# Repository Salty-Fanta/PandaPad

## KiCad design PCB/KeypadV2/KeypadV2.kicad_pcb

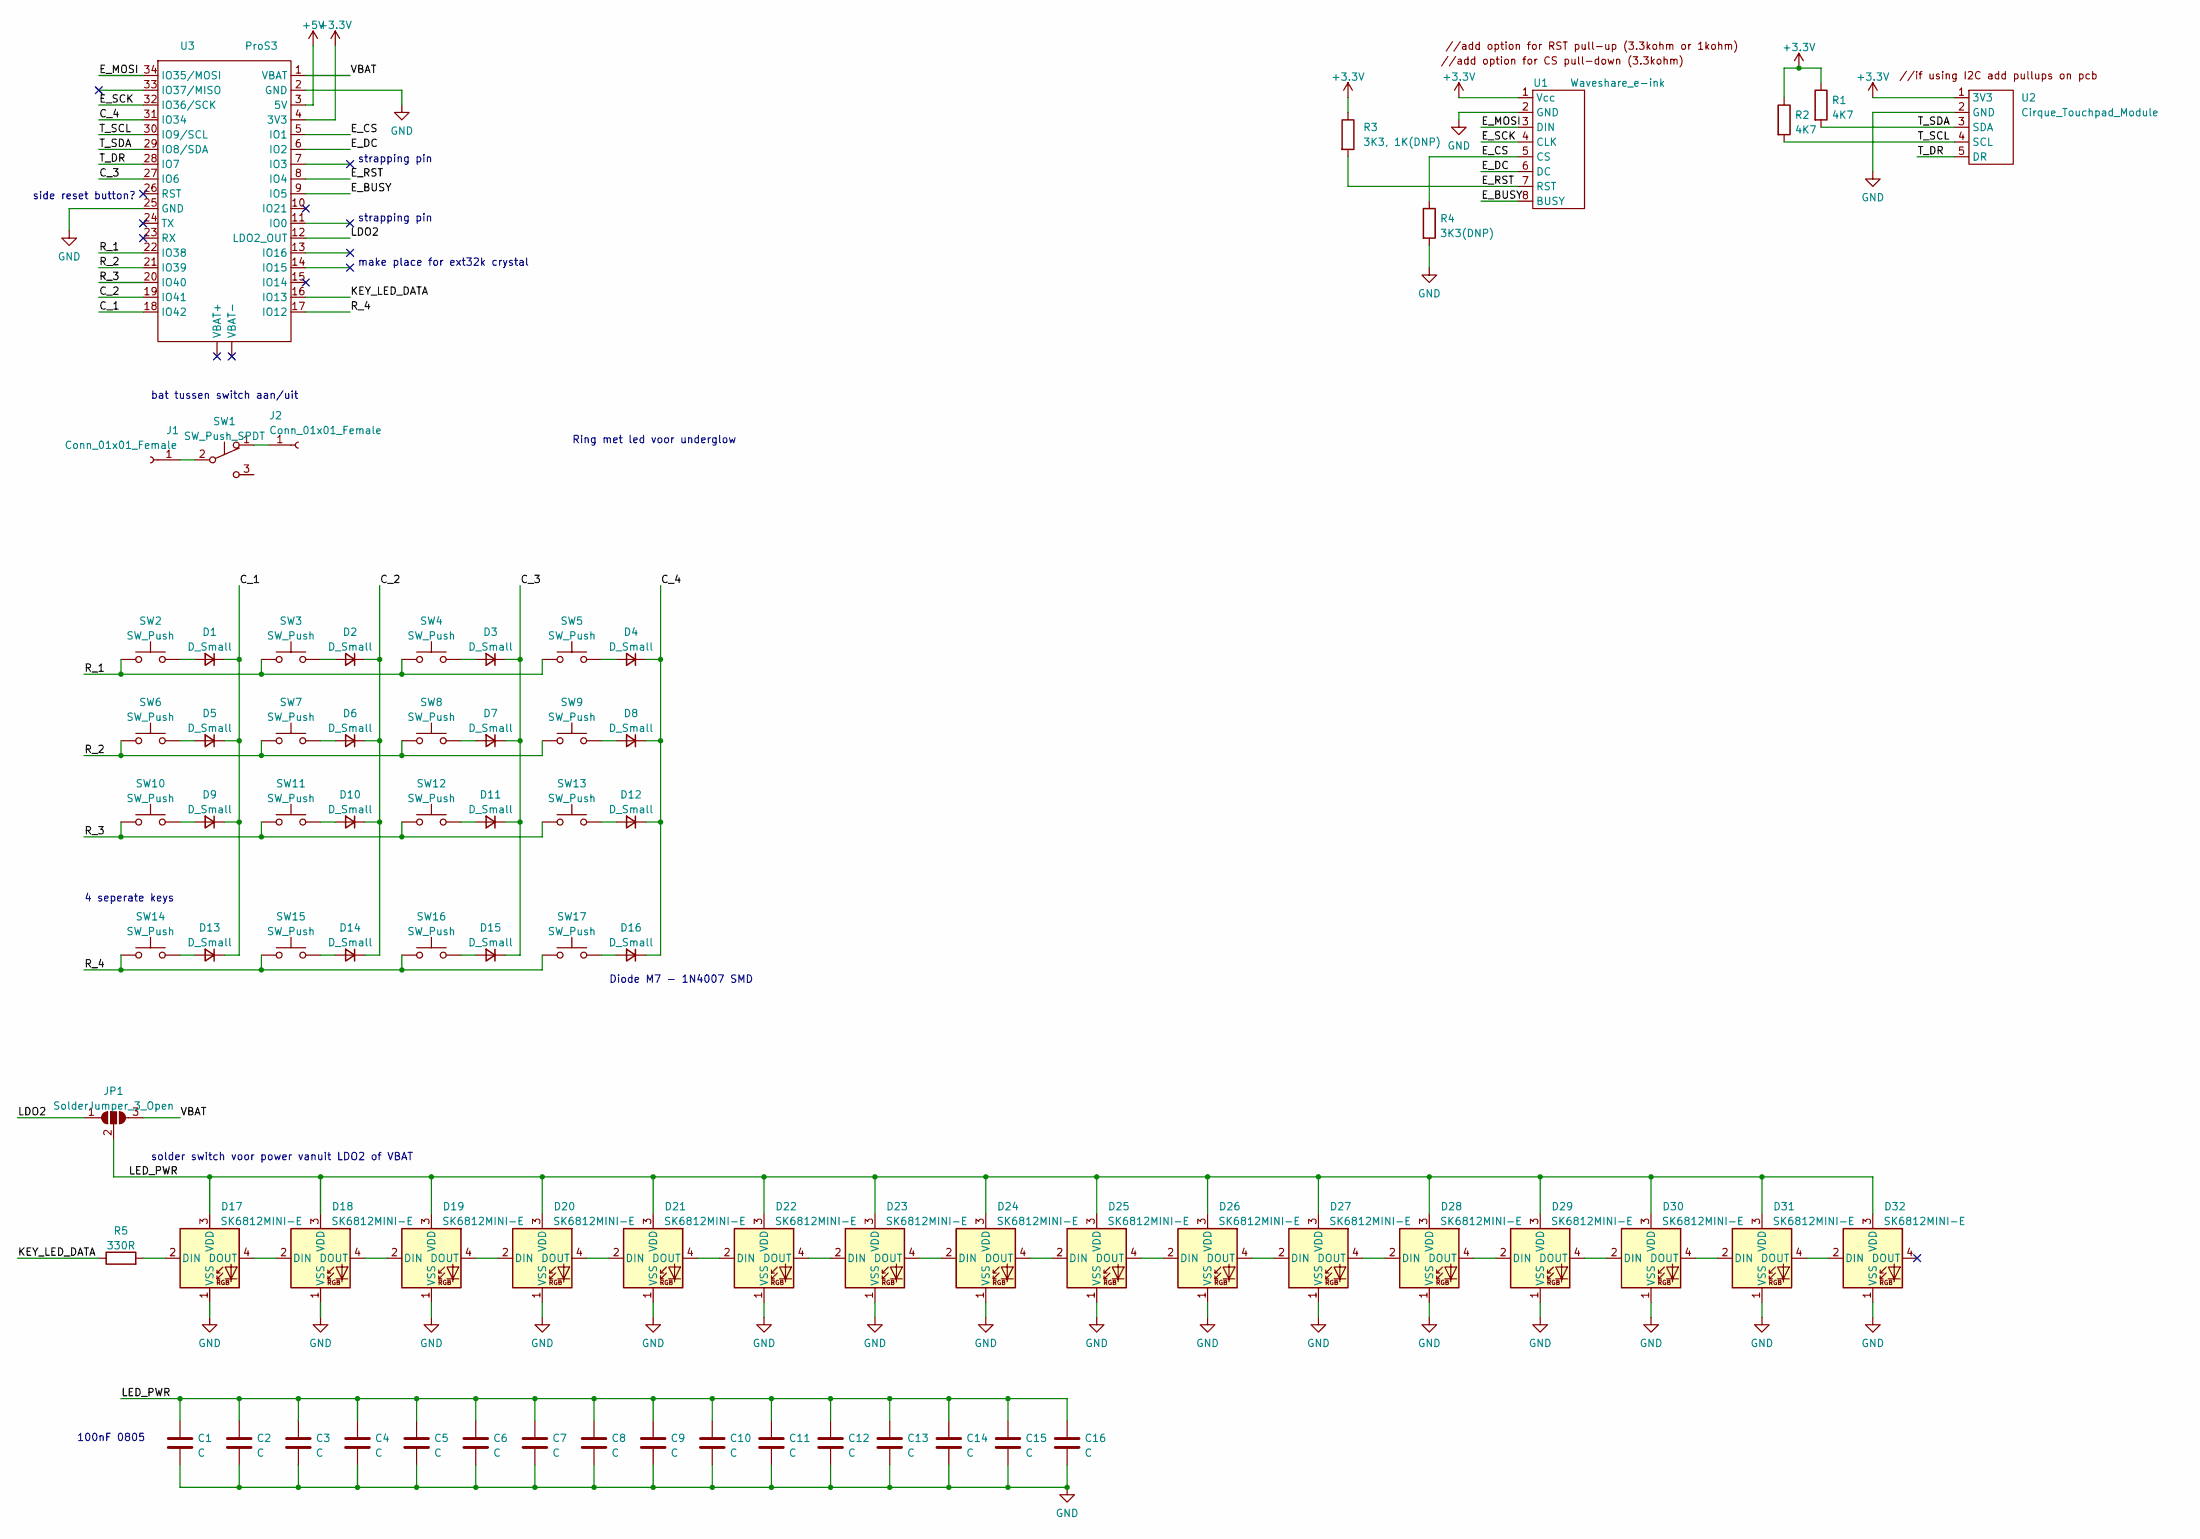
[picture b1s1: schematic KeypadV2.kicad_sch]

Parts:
C1, C2, C3, C4, C5, C6, C7, C8, C9, C10, C11, C12, C13, C14, C15, C16: C; C_0805_2012Metric_Pad1.18x1.45mm_HandSolder
D1, D2, D3, D4, D5, D6, D7, D8, D9, D10, D11, D12, D13, D14, D15, D16: D_Small; D_SOD-123
D17, D18, D19, D20, D21, D22, D23, D24, D25, D26, D27, D28, D29, D30, D31, D32: SK6812MINI-E; SK6812mini
J1, J2: Conn_01x01_Female; PinHeader_1x01_P2.54mm_Vertical
JP1: SolderJumper_3_Open; SolderJumper-3_P1.3mm_Open_Pad1.0x1.5mm
R1, R2: 4K7; R_0805_2012Metric_Pad1.20x1.40mm_HandSolder
R3: 3K3, 1K(DNP); R_0805_2012Metric_Pad1.20x1.40mm_HandSolder
R4: 3K3(DNP); R_0805_2012Metric_Pad1.20x1.40mm_HandSolder
R5: 330R; R_0805_2012Metric_Pad1.20x1.40mm_HandSolder
SW1: SW_Push_SPDT; PinHeader_1x03_P2.54mm_Vertical
SW2, SW3, SW4, SW5, SW6, SW7, SW8, SW9, SW10, SW11, SW12, SW13, SW14, SW15, SW16, SW17: SW_Push; Kailh_socket_MX
U1: Waveshare_e-ink; PinHeader_1x08_P2.54mm_Vertical
U2: Cirque_Touchpad_Module; PinHeader_1x05_P2.54mm_Vertical
U3: ProS3; ProS3_SMD

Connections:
+3.3V: R1.1, R2.1, R3.1, U1.1 (Vcc), U2.1 (3V3), U3.4 (3V3)
+5V: U3.3 (5V)
/C_1: D1.1 (K), D5.1 (K), D9.1 (K), D13.1 (K), U3.18 (IO42)
/C_2: D2.1 (K), D6.1 (K), D10.1 (K), D14.1 (K), U3.19 (IO41)
/C_3: D3.1 (K), D7.1 (K), D11.1 (K), D15.1 (K), U3.27 (IO6)
/C_4: D4.1 (K), D8.1 (K), D12.1 (K), D16.1 (K), U3.31 (IO34)
/E_BUSY: U1.8 (BUSY), U3.9 (IO5)
/E_CS: R4.1, U1.5 (CS), U3.5 (IO1)
/E_DC: U1.6 (DC), U3.6 (IO2)
/E_MOSI: U1.3 (DIN), U3.34 (IO35/MOSI)
/E_RST: R3.2, U1.7 (RST), U3.8 (IO4)
/E_SCK: U1.4 (CLK), U3.32 (IO36/SCK)
/KEY_LED_DATA: R5.1, U3.16 (IO13)
/LDO2: JP1.1 (A), U3.12 (LDO2_OUT)
/LED_PWR: C1.1, C2.1, C3.1, C4.1, C5.1, C6.1, C7.1, C8.1, C9.1, C10.1, C11.1, C12.1, C13.1, C14.1, C15.1, C16.1, D17.3 (VDD), D18.3 (VDD), D19.3 (VDD), D20.3 (VDD), D21.3 (VDD), D22.3 (VDD), D23.3 (VDD), D24.3 (VDD), D25.3 (VDD), D26.3 (VDD), D27.3 (VDD), D28.3 (VDD), D29.3 (VDD), D30.3 (VDD), D31.3 (VDD), D32.3 (VDD), JP1.2 (C)
/R_1: SW2.1, SW3.1, SW4.1, SW5.1, U3.22 (IO38)
/R_2: SW6.1, SW7.1, SW8.1, SW9.1, U3.21 (IO39)
/R_3: SW10.1, SW11.1, SW12.1, SW13.1, U3.20 (IO40)
/R_4: SW14.1, SW15.1, SW16.1, SW17.1, U3.17 (IO12)
/T_DR: U2.5 (DR), U3.28 (IO7)
/T_SCL: R2.2, U2.4 (SCL), U3.30 (IO9/SCL)
/T_SDA: R1.2, U2.3 (SDA), U3.29 (IO8/SDA)
/VBAT: JP1.3 (B), U3.1 (VBAT)
GND: C1.2, C2.2, C3.2, C4.2, C5.2, C6.2, C7.2, C8.2, C9.2, C10.2, C11.2, C12.2, C13.2, C14.2, C15.2, C16.2, D17.1 (VSS), D18.1 (VSS), D19.1 (VSS), D20.1 (VSS), D21.1 (VSS), D22.1 (VSS), D23.1 (VSS), D24.1 (VSS), D25.1 (VSS), D26.1 (VSS), D27.1 (VSS), D28.1 (VSS), D29.1 (VSS), D30.1 (VSS), D31.1 (VSS), D32.1 (VSS), R4.2, U1.2 (GND), U2.2 (GND), U3.2 (GND), U3.25 (GND)
unnamed: D1.2 (A), SW2.2
unnamed: D2.2 (A), SW3.2
unnamed: D3.2 (A), SW4.2
unnamed: D4.2 (A), SW5.2
unnamed: D5.2 (A), SW6.2
unnamed: D6.2 (A), SW7.2
unnamed: D7.2 (A), SW8.2
unnamed: D8.2 (A), SW9.2
unnamed: D9.2 (A), SW10.2
unnamed: D10.2 (A), SW11.2
unnamed: D11.2 (A), SW12.2
unnamed: D12.2 (A), SW13.2
unnamed: D13.2 (A), SW14.2
unnamed: D14.2 (A), SW15.2
unnamed: D15.2 (A), SW16.2
unnamed: D16.2 (A), SW17.2
unnamed: D17.2 (DIN), R5.2
unnamed: D17.4 (DOUT), D18.2 (DIN)
unnamed: D18.4 (DOUT), D19.2 (DIN)
unnamed: D19.4 (DOUT), D20.2 (DIN)
unnamed: D20.4 (DOUT), D21.2 (DIN)
unnamed: D21.4 (DOUT), D22.2 (DIN)
unnamed: D22.4 (DOUT), D23.2 (DIN)
unnamed: D23.4 (DOUT), D24.2 (DIN)
unnamed: D24.4 (DOUT), D25.2 (DIN)
unnamed: D25.4 (DOUT), D26.2 (DIN)
unnamed: D26.4 (DOUT), D27.2 (DIN)
unnamed: D27.4 (DOUT), D28.2 (DIN)
unnamed: D28.4 (DOUT), D29.2 (DIN)
unnamed: D29.4 (DOUT), D30.2 (DIN)
unnamed: D30.4 (DOUT), D31.2 (DIN)
unnamed: D31.4 (DOUT), D32.2 (DIN)
unnamed: J1.1, SW1.2 (B)
unnamed: J2.1, SW1.1 (A)

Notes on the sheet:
Ring met led voor underglow
4 seperate keys
solder switch voor power vanuit LDO2 of VBAT
100nF 0805
make place for ext32k crystal
Diode M7 - 1N4007 SMD
strapping pin
bat tussen switch aan/uit
side reset button?

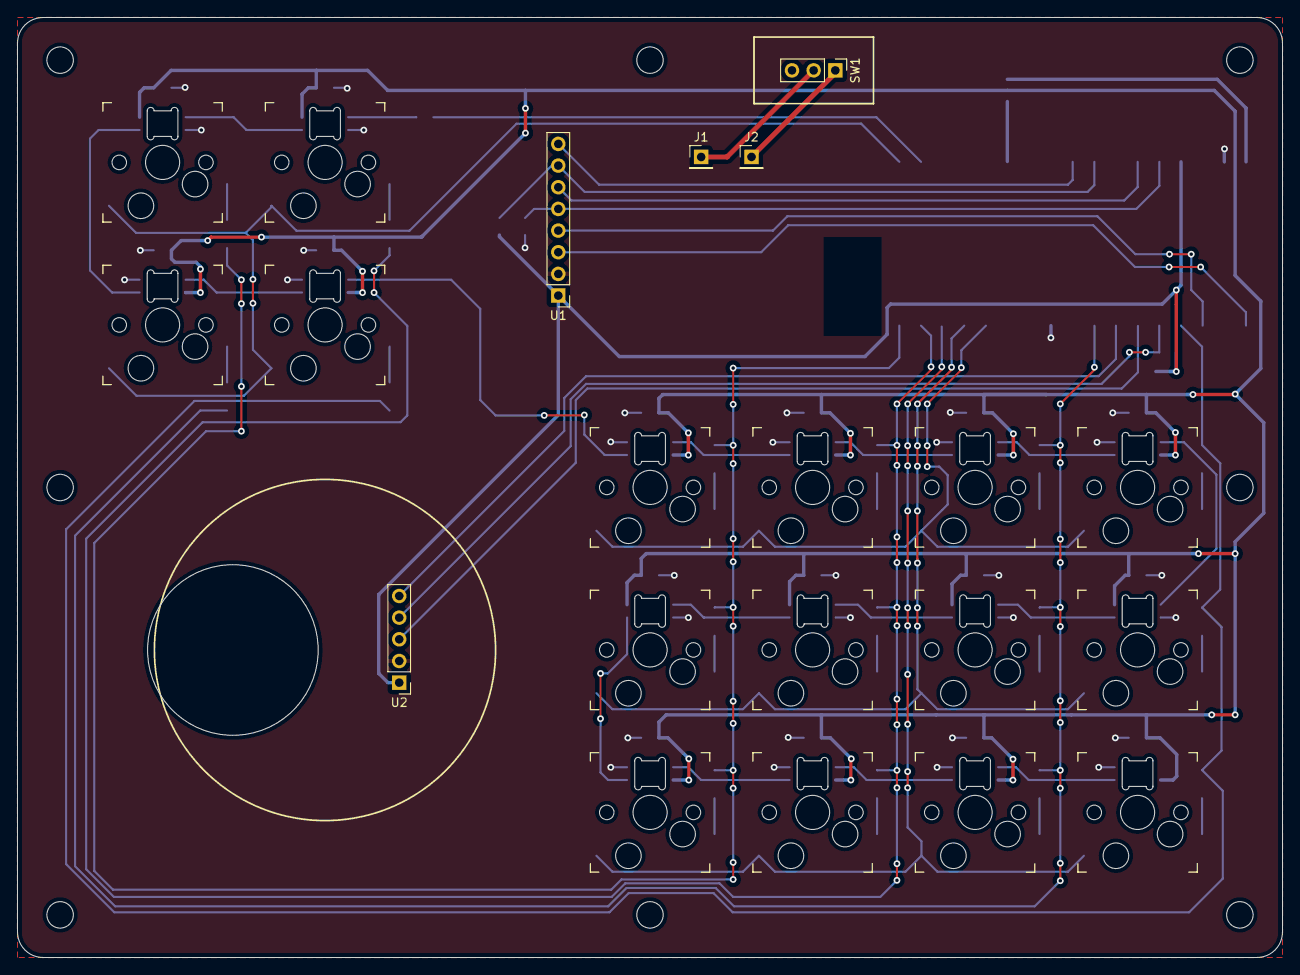
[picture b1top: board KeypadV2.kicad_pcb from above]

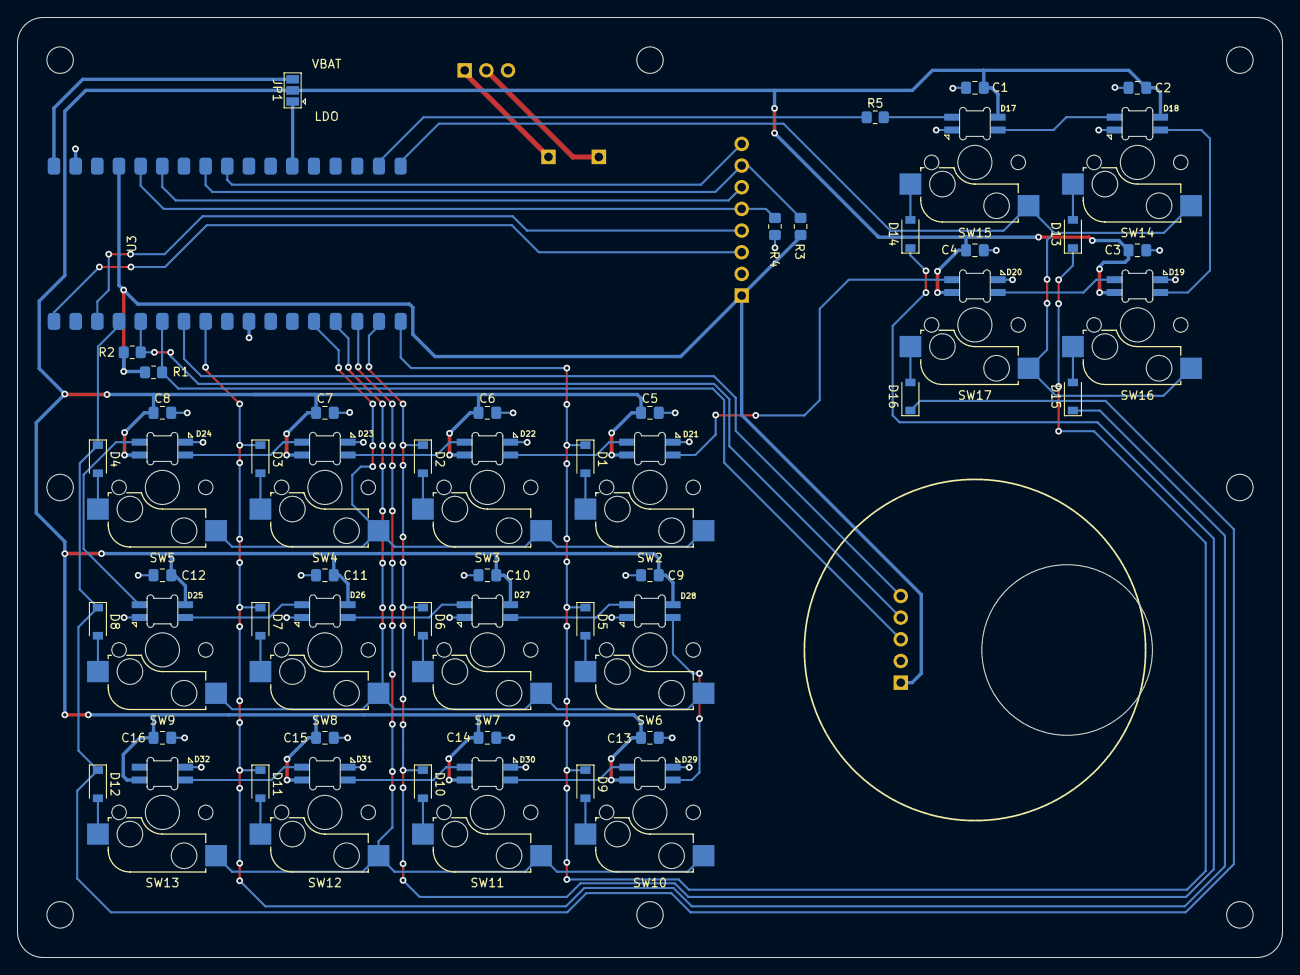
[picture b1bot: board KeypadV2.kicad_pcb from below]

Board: 2 copper layers, 148.3 x 110.2 mm, 76 parts (55 on the bottom side), 57 nets.

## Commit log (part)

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2023-07-13 Added PCB files, STL's and first firmware tests
2023-07-13 Tested keypad functionality
2023-07-14 Added .gitignore and deleted ignored files
2023-07-15 combined test versions into first basic release.
2023-07-25 Added Carry_Case_Base.stl and Carry_Case_Lid.stl
2023-07-31 Used Keypad getkeys to buffer multiple keys and get around the different keys debounce issue. Added elapsed loops per second counter to serial monitor debug.
2023-08-02 fix compile error missing break;
2024-04-16 Initial vscode setup.
2024-04-17 first test with working cmake and led test.
2024-04-20 basic keypad functionality. Only displays key and event in serial monitor, no actual functions yet. uses espressif/button.
2024-04-21 Next version with reactive backlight upon pressing a button.
2024-05-16 got absolute trackpad touch data in serial log working
2024-05-20 Updated the i2c driver to the not deprecated version.
